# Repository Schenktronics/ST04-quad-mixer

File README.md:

<picture>
  <source media="(prefers-color-scheme: dark)" srcset="docs/images/logo-light.png">
  
</picture>

# ST-04 Quad Mixer

A 6HP Eurorack four-channel active mixer from **Schenktronics**. Each channel has an input jack and a level knob that takes it from silent up to its own level. The four channels are summed into two outputs: a non-inverting mix (+) and an inverted one (-). Unplugged inputs are silent, so only the channels you patch affect the mix.

## Features

- 6HP (30 mm wide), 20 mm deep, powered from ±12 V
- Four channels, each with a level knob from silent to x1
- Two outputs: + (the mix) and - (the mix, inverted)
- Empty inputs are silent, so unused channels add nothing
- Reverse-power protection on both rails
- Kits come with the surface-mount parts already soldered and tested: 48 through-hole joints to build

## Documentation

| Document | For | PDF |
|----------|-----|-----|
| [User Manual](docs/manual.md) | Using the module | [PDF](docs/pdf/ST-04_Quad_Mixer_User_Manual.pdf) |
| [Assembly Guide](docs/assembly-guide.md) | Building the kit | [PDF](docs/pdf/ST-04_Quad_Mixer_Assembly_Guide.pdf) |
| [Bill of Materials](docs/BOM.md) ([CSV](docs/BOM.csv)) | Parts and sourcing | |

## Repository layout

```
hardware/
  ST-04_Quad Mixer.step           3D model of the assembled module
  mixer/                          Main PCB (KiCad 10)
    4ch Mixer.kicad_sch             Schematic
    4ch Mixer.kicad_pcb             PCB layout
    4ch Mixer.step                  3D model
    lib/                            Custom symbols and footprints
  panel/                          Faceplate (KiCad 10, made as an aluminum PCB)
    4ch Mixer Faceplate.kicad_pcb   Faceplate layout
    4ch Mixer Faceplate.step        3D model
docs/                             Manual, assembly guide, BOM, images
  pdf/                              PDF versions of the manual and assembly guide
```

The `.github/` folder holds the automation that builds the PDFs. You can ignore it.

## Fabrication

| Board | Size | Layers | Thickness | Notes |
|-------|------|--------|-----------|-------|
| Main PCB | 30 x 100 mm | 2 | 1.6 mm | Standard green is fine. Surface-mount parts on the back. |
| Faceplate | 30 x 128.5 mm | 1 | 1.6 mm | Aluminum PCB, white solder mask, black silkscreen. Only the front copper layer is used, so FR4 works too. |

## Sourcing your own parts

The [BOM](docs/BOM.md) lists every part, including the surface-mount ones the kits ship with already soldered. The jack pads are oval so the board can also take panel-mount style jacks, which may be easier to source. The CUI MJ-3507 is one example: its sleeve is a solder lug rather than a pin, so each one needs a short wire from that lug to the jack's square pad.

## License

This hardware design and its documentation are licensed under [CC BY-NC-SA 4.0](https://creativecommons.org/licenses/by-nc-sa/4.0/). See [LICENSE](LICENSE).

The Schenktronics name and logo are trademarks of Schenktronics LLC and are not covered by the CC BY-NC-SA 4.0 license.

## Links

- Shop: <https://schenktronics.com/product/st-04/>
- Docs page: <https://schenktronics.com/docs/st-04/>
- Website: <https://schenktronics.com>

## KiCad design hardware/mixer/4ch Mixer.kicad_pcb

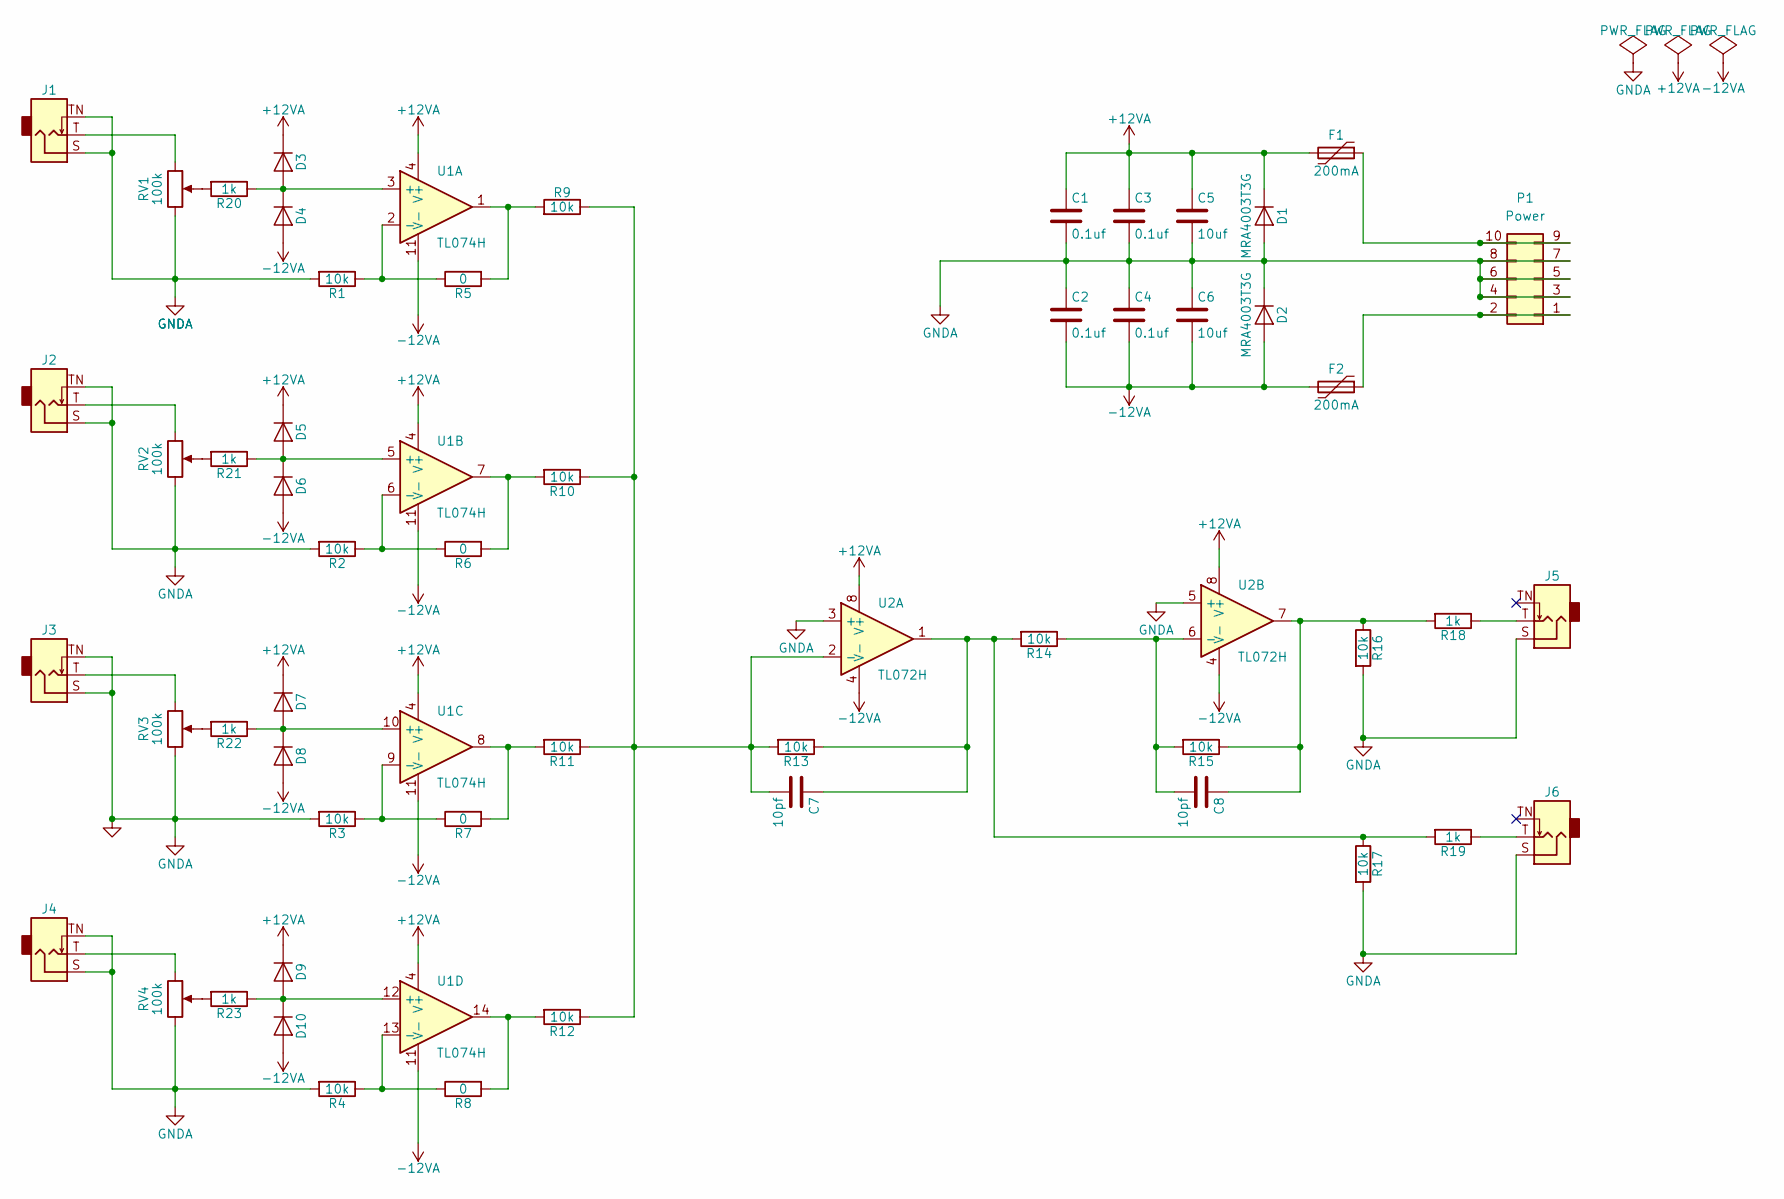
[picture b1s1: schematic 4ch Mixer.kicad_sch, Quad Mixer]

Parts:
C1, C2, C3, C4: 0.1uf; C_0805_2012Metric
C5, C6: 10uf; C_0805_2012Metric
C7, C8: 10pf; C_0805_2012Metric
D1, D2: MRA4003T3G; D_SMA
D3, D4, D5, D6, D7, D8, D9, D10: 1N4148; D_SOD-323
F1, F2: 200mA; Fuse_1206_3216Metric
J1, J2, J3, J4, J5, J6: Jack_3.5mm_QingPu_WQP-PJ398SM_Vertical_CenterHole_OvalPads
P1: Power; PinHeader_2x05_P2.54mm_Vertical_Shrouded
R1, R2, R3, R4, R9, R10, R11, R12, R13, R14, R15, R16, R17: 10k; R_0805_2012Metric
R5, R6, R7, R8: 0; R_0805_2012Metric
R18, R19, R20, R21, R22, R23: 1k; R_0805_2012Metric
RV1, RV2, RV3, RV4: 100k; Potentiometer_Alps_RK09L_Plated_Mount_Holes
U1: TL074H; SOIC-14_3.9x8.7mm_P1.27mm
U2: TL072H; SOIC-8_3.9x4.9mm_P1.27mm

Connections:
+12VA: C1.1, C3.1, C5.1, D1.1 (K), D3.1 (K), D5.1 (K), D7.1 (K), D9.1 (K), F1.2, U1.4 (V+), U2.8 (V+)
-12VA: C2.2, C4.2, C6.2, D2.2 (A), D4.2 (A), D6.2 (A), D8.2 (A), D10.2 (A), F2.2, U1.11 (V-), U2.4 (V-)
GNDA: C1.2, C2.1, C3.2, C4.1, C5.2, C6.1, D1.2 (A), D2.1 (K), J1.S, J1.TN, J2.S, J2.TN, J3.S, J3.TN, J4.S, J4.TN, J5.S, J6.S, P1.3, P1.4, P1.5, P1.6, P1.7, P1.8, R1.2, R2.2, R3.2, R4.2, R16.2, R17.2, RV1.3, RV2.3, RV3.3, RV4.3, U2.3 (+), U2.5 (+)
unnamed: D3.2 (A), D4.1 (K), R20.1, U1.3 (+)
unnamed: D5.2 (A), D6.1 (K), R21.1, U1.5 (+)
unnamed: D7.2 (A), D8.1 (K), R22.1, U1.10 (+)
unnamed: D9.2 (A), D10.1 (K), R23.1, U1.12 (+)
unnamed: J1.T, RV1.1
unnamed: J2.T, RV2.1
unnamed: J3.T, RV3.1
unnamed: J4.T, RV4.1
unnamed: J5.T, R18.1
unnamed: J6.T, R19.1
unnamed: F2.1, P1.1, P1.2
unnamed: F1.1, P1.9, P1.10
unnamed: R20.2, RV1.2
unnamed: R21.2, RV2.2
unnamed: R22.2, RV3.2
unnamed: R23.2, RV4.2
unnamed: R1.1, R5.1, U1.2 (-)
unnamed: R5.2, R9.2, U1.1
unnamed: R2.1, R6.1, U1.6 (-)
unnamed: R6.2, R10.2, U1.7
unnamed: R3.1, R7.1, U1.9 (-)
unnamed: R7.2, R11.2, U1.8
unnamed: R4.1, R8.1, U1.13 (-)
unnamed: R8.2, R12.2, U1.14
unnamed: C7.2, R9.1, R10.1, R11.1, R12.1, R13.2, U2.2 (-)
unnamed: C7.1, R13.1, R14.2, R17.1, R19.2, U2.1
unnamed: C8.2, R14.1, R15.2, U2.6 (-)
unnamed: C8.1, R15.1, R16.1, R18.2, U2.7

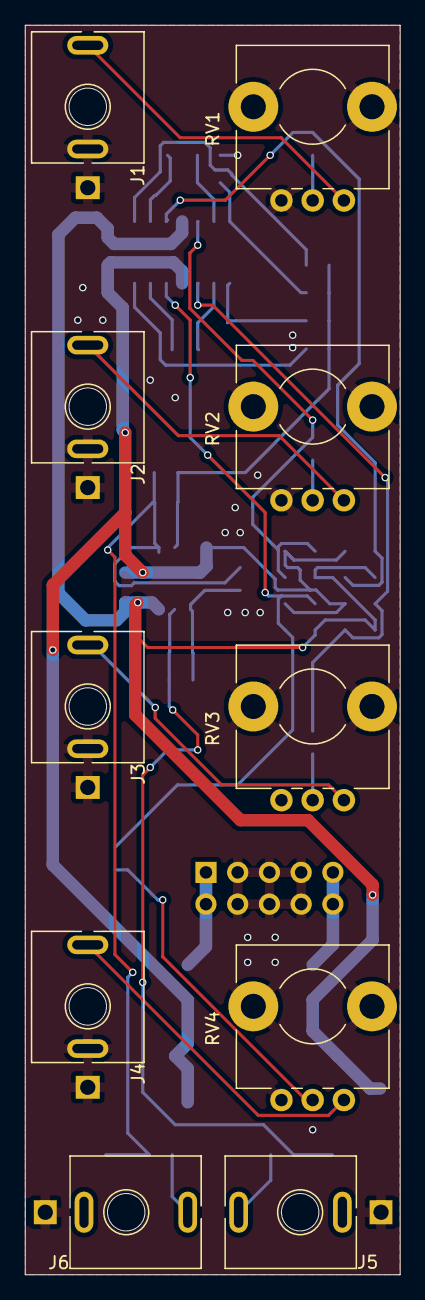
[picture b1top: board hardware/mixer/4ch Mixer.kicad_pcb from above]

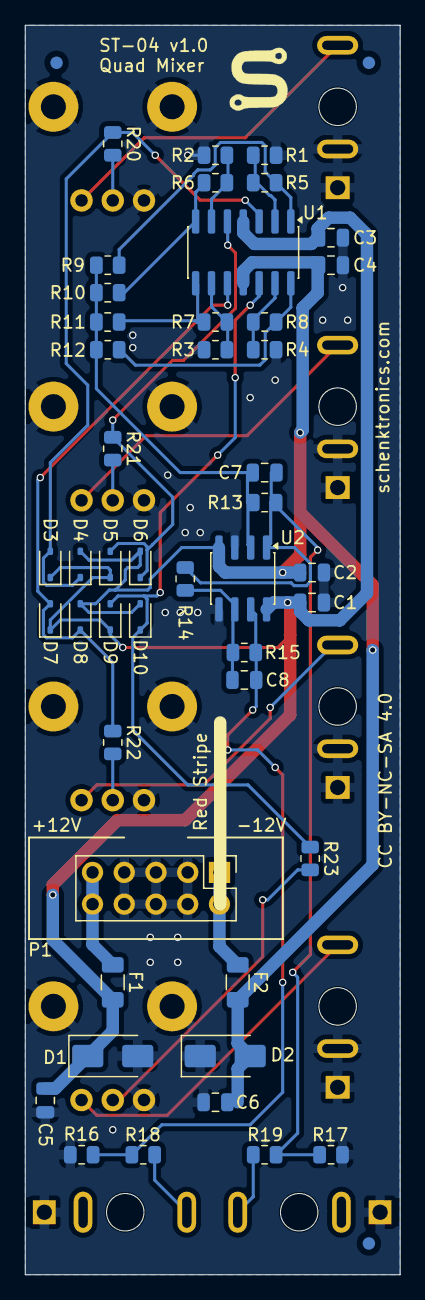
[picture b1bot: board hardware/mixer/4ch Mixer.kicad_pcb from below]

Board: 2 copper layers, 30.0 x 100.0 mm, 59 parts (49 on the bottom side), 31 nets.

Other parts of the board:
FID1, FID2, FID3: Fiducial_1mm_Mask2mm

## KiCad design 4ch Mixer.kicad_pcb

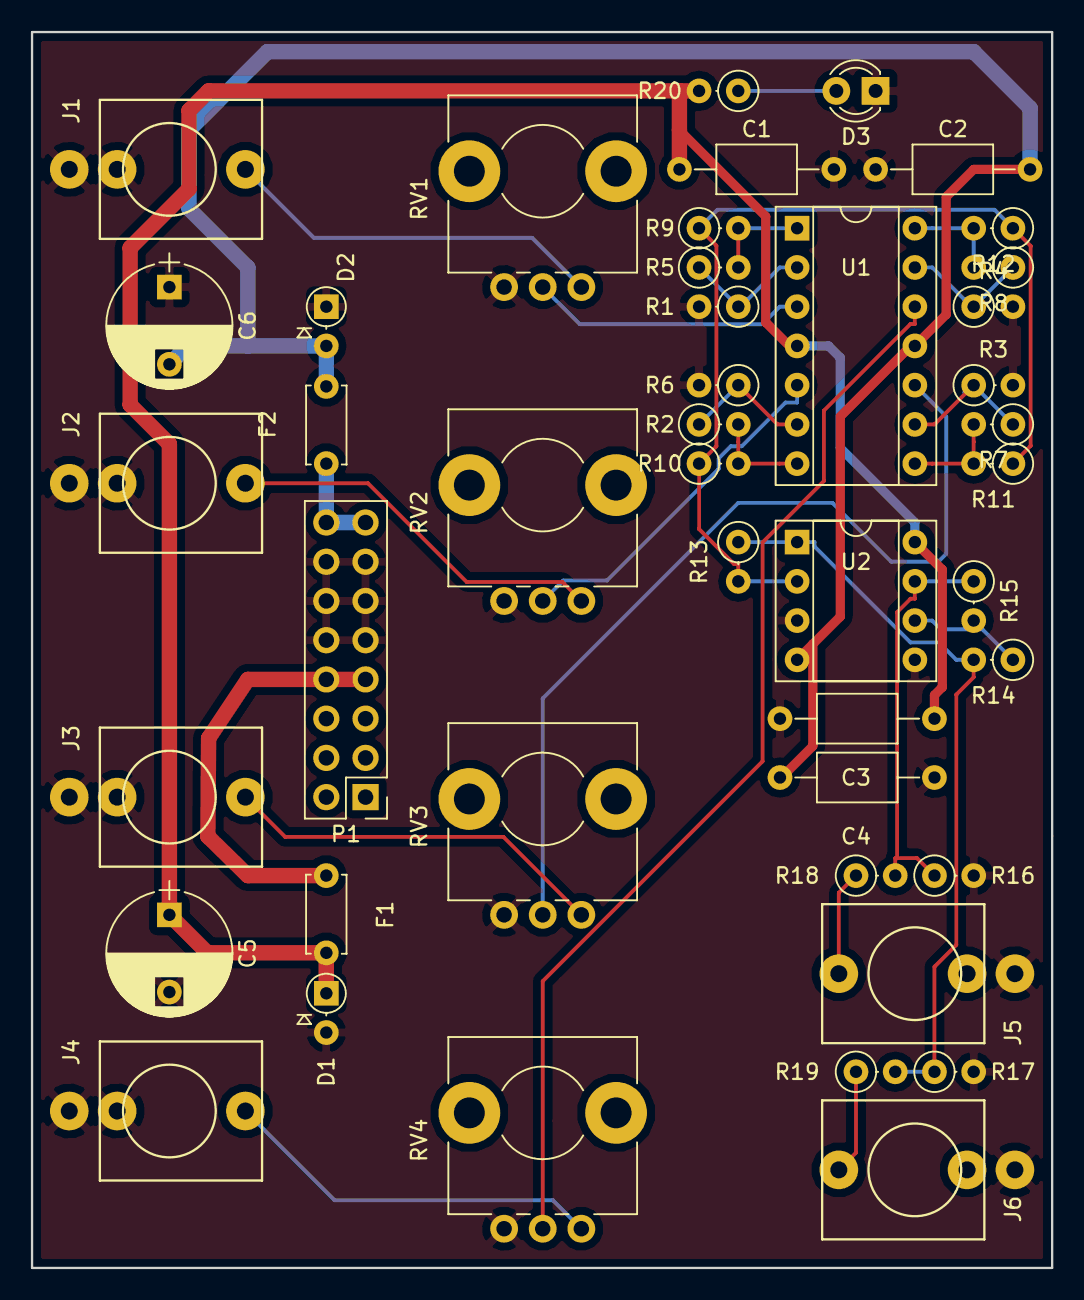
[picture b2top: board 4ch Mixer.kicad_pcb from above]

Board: 2 copper layers, 66.0 x 80.0 mm, 44 parts (0 on the bottom side), 28 nets.

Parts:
C1, C2, C3, C4: 0.1uf; C_Axial_L5.1mm_D3.1mm_P10.00mm_Horizontal
C5, C6: 100uf; CP_Radial_D8.0mm_P5.00mm
D1, D2: 1N4002; D_DO-35_SOD27_P2.54mm_Vertical_AnodeUp
D3: LED; LED_D3.0mm
F1, F2: 250mA; C_Disc_D5.0mm_W2.5mm_P5.00mm
J1, J2, J3, J4, J5, J6: 3.5mm_Mono_Jack_With_Switch; 3.5mm_Mono_Vertical_QuingPu_WQP-PJ301M-12
P1: CONN_02X08; Pin_Header_Straight_2x08_Pitch2.54mm
R1, R2, R3, R4, R5, R6, R7, R8, R9, R10, R11, R12, R13, R14, R15, R16, R17: 10k; R_Axial_DIN0207_L6.3mm_D2.5mm_P2.54mm_Vertical
R18, R19: 100; R_Axial_DIN0207_L6.3mm_D2.5mm_P2.54mm_Vertical
R20: 1k; R_Axial_DIN0207_L6.3mm_D2.5mm_P2.54mm_Vertical
RV1, RV2, RV3, RV4: 100k; Potentiometer_Alps_RK09L_Sleve_Single_Horizontal
U1: TL074; DIP-14_W7.62mm_Socket
U2: TL072; DIP-8_W7.62mm_Socket

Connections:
+12VA: C1.1, C3.1, C5.1, D1.1, F1.2, R20.2, U1.4, U2.8
-12VA: C2.2, C4.2, C6.2, D2.2, F2.2, U1.11, U2.4
GNDA: C1.2, C2.1, C3.2, C4.1, C5.2, C6.1, D1.2, D2.1, D3.1, J1.1, J1.2, J2.1, J2.2, J3.1, J3.2, J4.1, J4.2, J5.1, J6.1, P1.9, P1.10, P1.11, P1.12, P1.13, P1.14, R1.2, R2.2, R3.2, R4.2, R16.2, R17.2, RV1.3, RV2.3, RV3.3, RV4.3, U2.3, U2.5
unnamed: D3.2, R20.1
unnamed: F1.1, P1.7, P1.8
unnamed: F2.1, P1.15, P1.16
unnamed: J1.3, RV1.1
unnamed: J2.3, RV2.1
unnamed: J3.3, RV3.1
unnamed: J4.3, RV4.1
unnamed: J5.3, R18.1
unnamed: J6.3, R19.1
unnamed: R1.1, R5.1, U1.2
unnamed: R2.1, R6.1, U1.6
unnamed: R3.1, R7.1, U1.9
unnamed: R4.1, R8.1, U1.13
unnamed: R5.2, R9.2, U1.1
unnamed: R9.1, R10.1, R11.1, R12.1, R13.2, U2.2
unnamed: R6.2, R10.2, U1.7
unnamed: R7.2, R11.2, U1.8
unnamed: R8.2, R12.2, U1.14
unnamed: R13.1, R14.2, R17.1, R19.2, U2.1
unnamed: R14.1, R15.2, U2.6
unnamed: R15.1, R16.1, R18.2, U2.7
unnamed: RV1.2, U1.3
unnamed: RV2.2, U1.5
unnamed: RV3.2, U1.10
unnamed: RV4.2, U1.12

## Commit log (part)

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2017-02-12 Initial Commit. Built prototype board and tested.
2017-02-12 Added Faceplate and laser program
2017-02-13 Renamed drawing to reflect hp use
2017-02-22 Added 100 ohm resistors to outputs. This is to prevent oscillations when using high capacitance cables.
2017-02-22 Added PTC fuses and protection diodes to schematic.
    Associated footprints.
    Started a PCB layout, need to update some footprints.
2017-02-23 Continued work on PCB and Schematic
2017-02-23 Worked on the PCB
2017-03-08 Created PCB. Need to look over carefully.
    Need to measure potentiometer footprint to ensure it is correct.
2017-03-08 Made some gerbers.
    Need to redo the board layout to fit 12hp max.
    55mm x 100mm, or better yet 45mm x 100mm
2017-03-09 Moved Schematic/Board Layout to its own folder
2017-03-09 Build a new PCB layout with a smaller footprint
2017-03-09 I think the board is done
2017-03-09 Minor edits. Added Gerbers.zip.
2017-03-09 Added caps to final op amp feedback.
    Moved big bypass caps to backside of board.
    Added mounting hole.
    Generated new Gerbers
2017-03-10 Created faceplate dwg
2017-03-10 Created faceplate dxf.
2017-07-12 Initial Laser Work
2018-01-16 General Commit
